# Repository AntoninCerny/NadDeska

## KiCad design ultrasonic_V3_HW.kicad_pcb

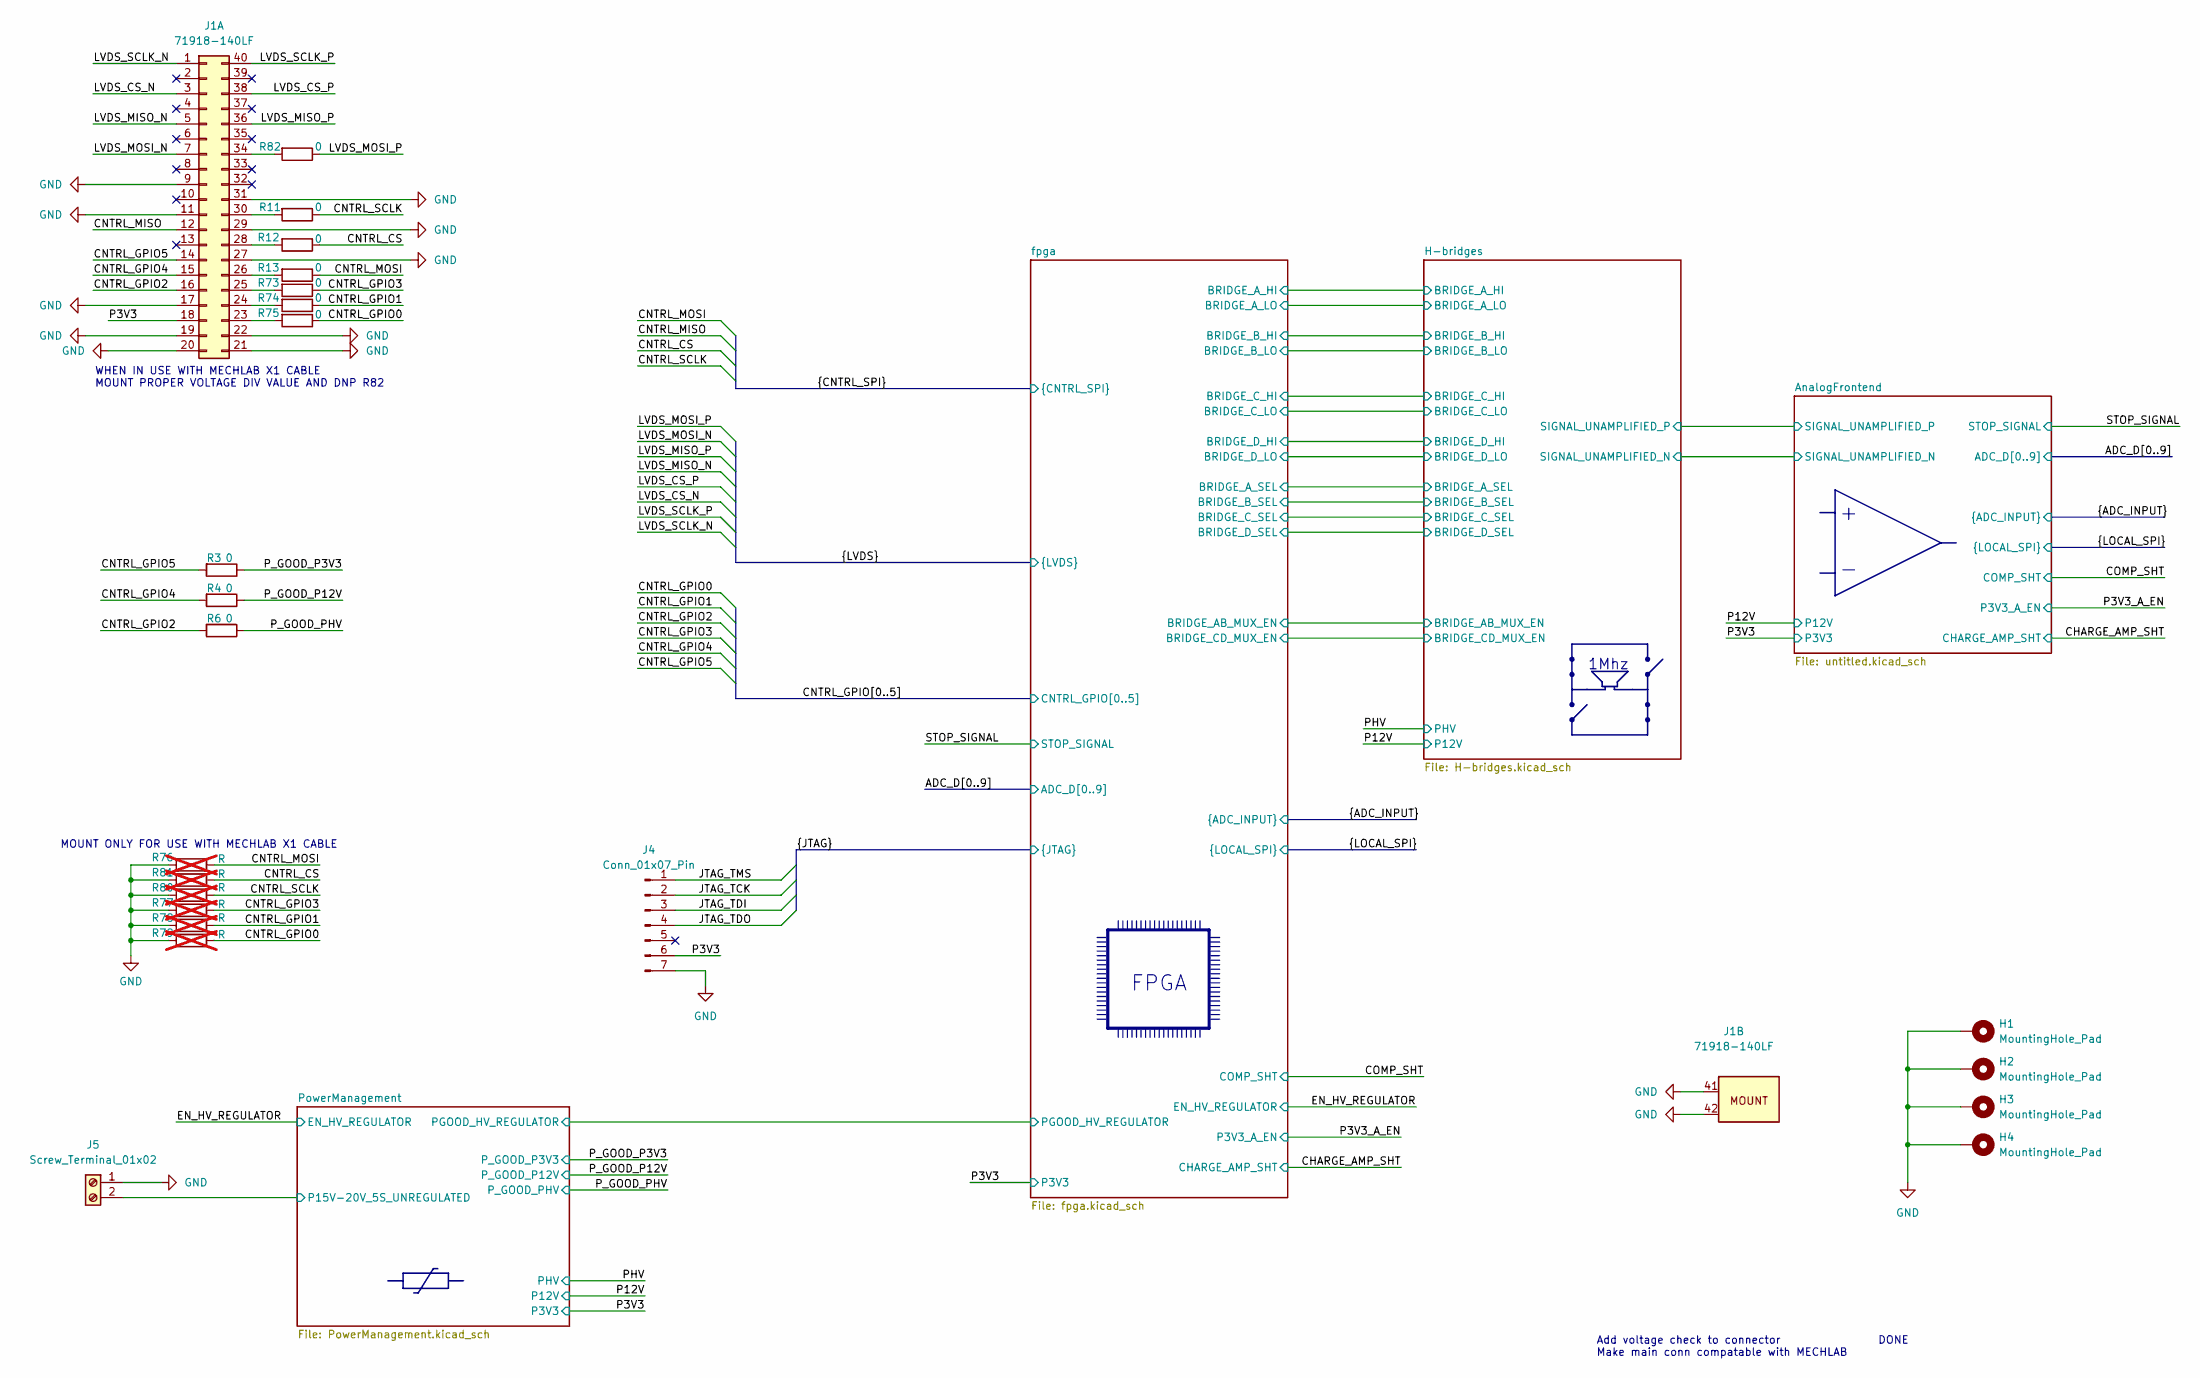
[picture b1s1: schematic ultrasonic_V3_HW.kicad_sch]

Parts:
H1, H2, H3, H4: MountingHole_Pad; MountingHole_3.2mm_M3_DIN965_Pad_TopBottom
J1: 71918-140LF; CON40_2X20_USZ_FCI_GLE
J4: Conn_01x07_Pin; PinHeader_1x07_P2.54mm_Vertical
J5: Screw_Terminal_01x02; TerminalBlock_Phoenix_MKDS-1,5-2-5.08_1x02_P5.08mm_Horizont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
R3, R4, R6, R11, R12, R13, R73, R74, R75, R82: 0; R_0603_1608Metric_Pad0.98x0.95mm_HandSolder
R76, R77, R78, R79, R80, R81: R; R_0603_1608Metric_Pad0.98x0.95mm_HandSolder; not fitted

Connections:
/CNTRL_CS: R12.1, R81.1; also elsewhere on the board
/CNTRL_GPIO0: R75.1, R79.1; also elsewhere on the board
/CNTRL_GPIO1: R74.1, R78.1; also elsewhere on the board
/CNTRL_GPIO2: J1.16, R6.2; also elsewhere on the board
/CNTRL_GPIO3: R73.1, R77.1; also elsewhere on the board
/CNTRL_GPIO4: J1.15, R4.2; also elsewhere on the board
/CNTRL_GPIO5: J1.14, R3.2; also elsewhere on the board
/CNTRL_MISO: J1.12; also elsewhere on the board
/CNTRL_MOSI: R13.1, R76.1; also elsewhere on the board
/CNTRL_SCLK: R11.1, R80.1; also elsewhere on the board
/JTAG_TCK: J4.2; also elsewhere on the board
/JTAG_TDI: J4.3; also elsewhere on the board
/JTAG_TDO: J4.4; also elsewhere on the board
/JTAG_TMS: J4.1; also elsewhere on the board
/LVDS_CS_N: J1.3; also elsewhere on the board
/LVDS_CS_P: J1.38; also elsewhere on the board
/LVDS_MISO_N: J1.5; also elsewhere on the board
/LVDS_MISO_P: J1.36; also elsewhere on the board
/LVDS_MOSI_N: J1.7; also elsewhere on the board
/LVDS_MOSI_P: R82.1; also elsewhere on the board
/LVDS_SCLK_N: J1.1; also elsewhere on the board
/LVDS_SCLK_P: J1.40; also elsewhere on the board
/P3V3: J1.18, J4.6; also elsewhere on the board
/P_GOOD_P3V3: R3.1; also elsewhere on the board
/P_GOOD_P12V: R4.1; also elsewhere on the board
/P_GOOD_PHV: R6.1; also elsewhere on the board
/PowerManagement/P15V-20V_5S_UNREGULATED: J5.2; also elsewhere on the board
GND: H1.1, H2.1, H3.1, H4.1, J1.9, J1.11, J1.17, J1.19, J1.20, J1.21, J1.22, J1.27, J1.29, J1.31, J1.41 (MOUNT_HOLE), J1.42 (MOUNT_HOLE), J4.7, J5.1, R76.2, R77.2, R78.2, R79.2, R80.2, R81.2; also elsewhere on the board
unnamed: J1.23, R75.2
unnamed: J1.24, R74.2
unnamed: J1.25, R73.2
unnamed: J1.26, R13.2
unnamed: J1.28, R12.2
unnamed: J1.30, R11.2
unnamed: J1.34, R82.2

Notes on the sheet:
FPGA
WHEN IN USE WITH MECHLAB X1 CABLE MOUNT PROPER VOLTAGE DIV VALUE AND DNP R82
Add voltage check to connector DONE Make main conn compatable with MECHLAB
MOUNT ONLY FOR USE WITH MECHLAB X1 CABLE
1Mhz

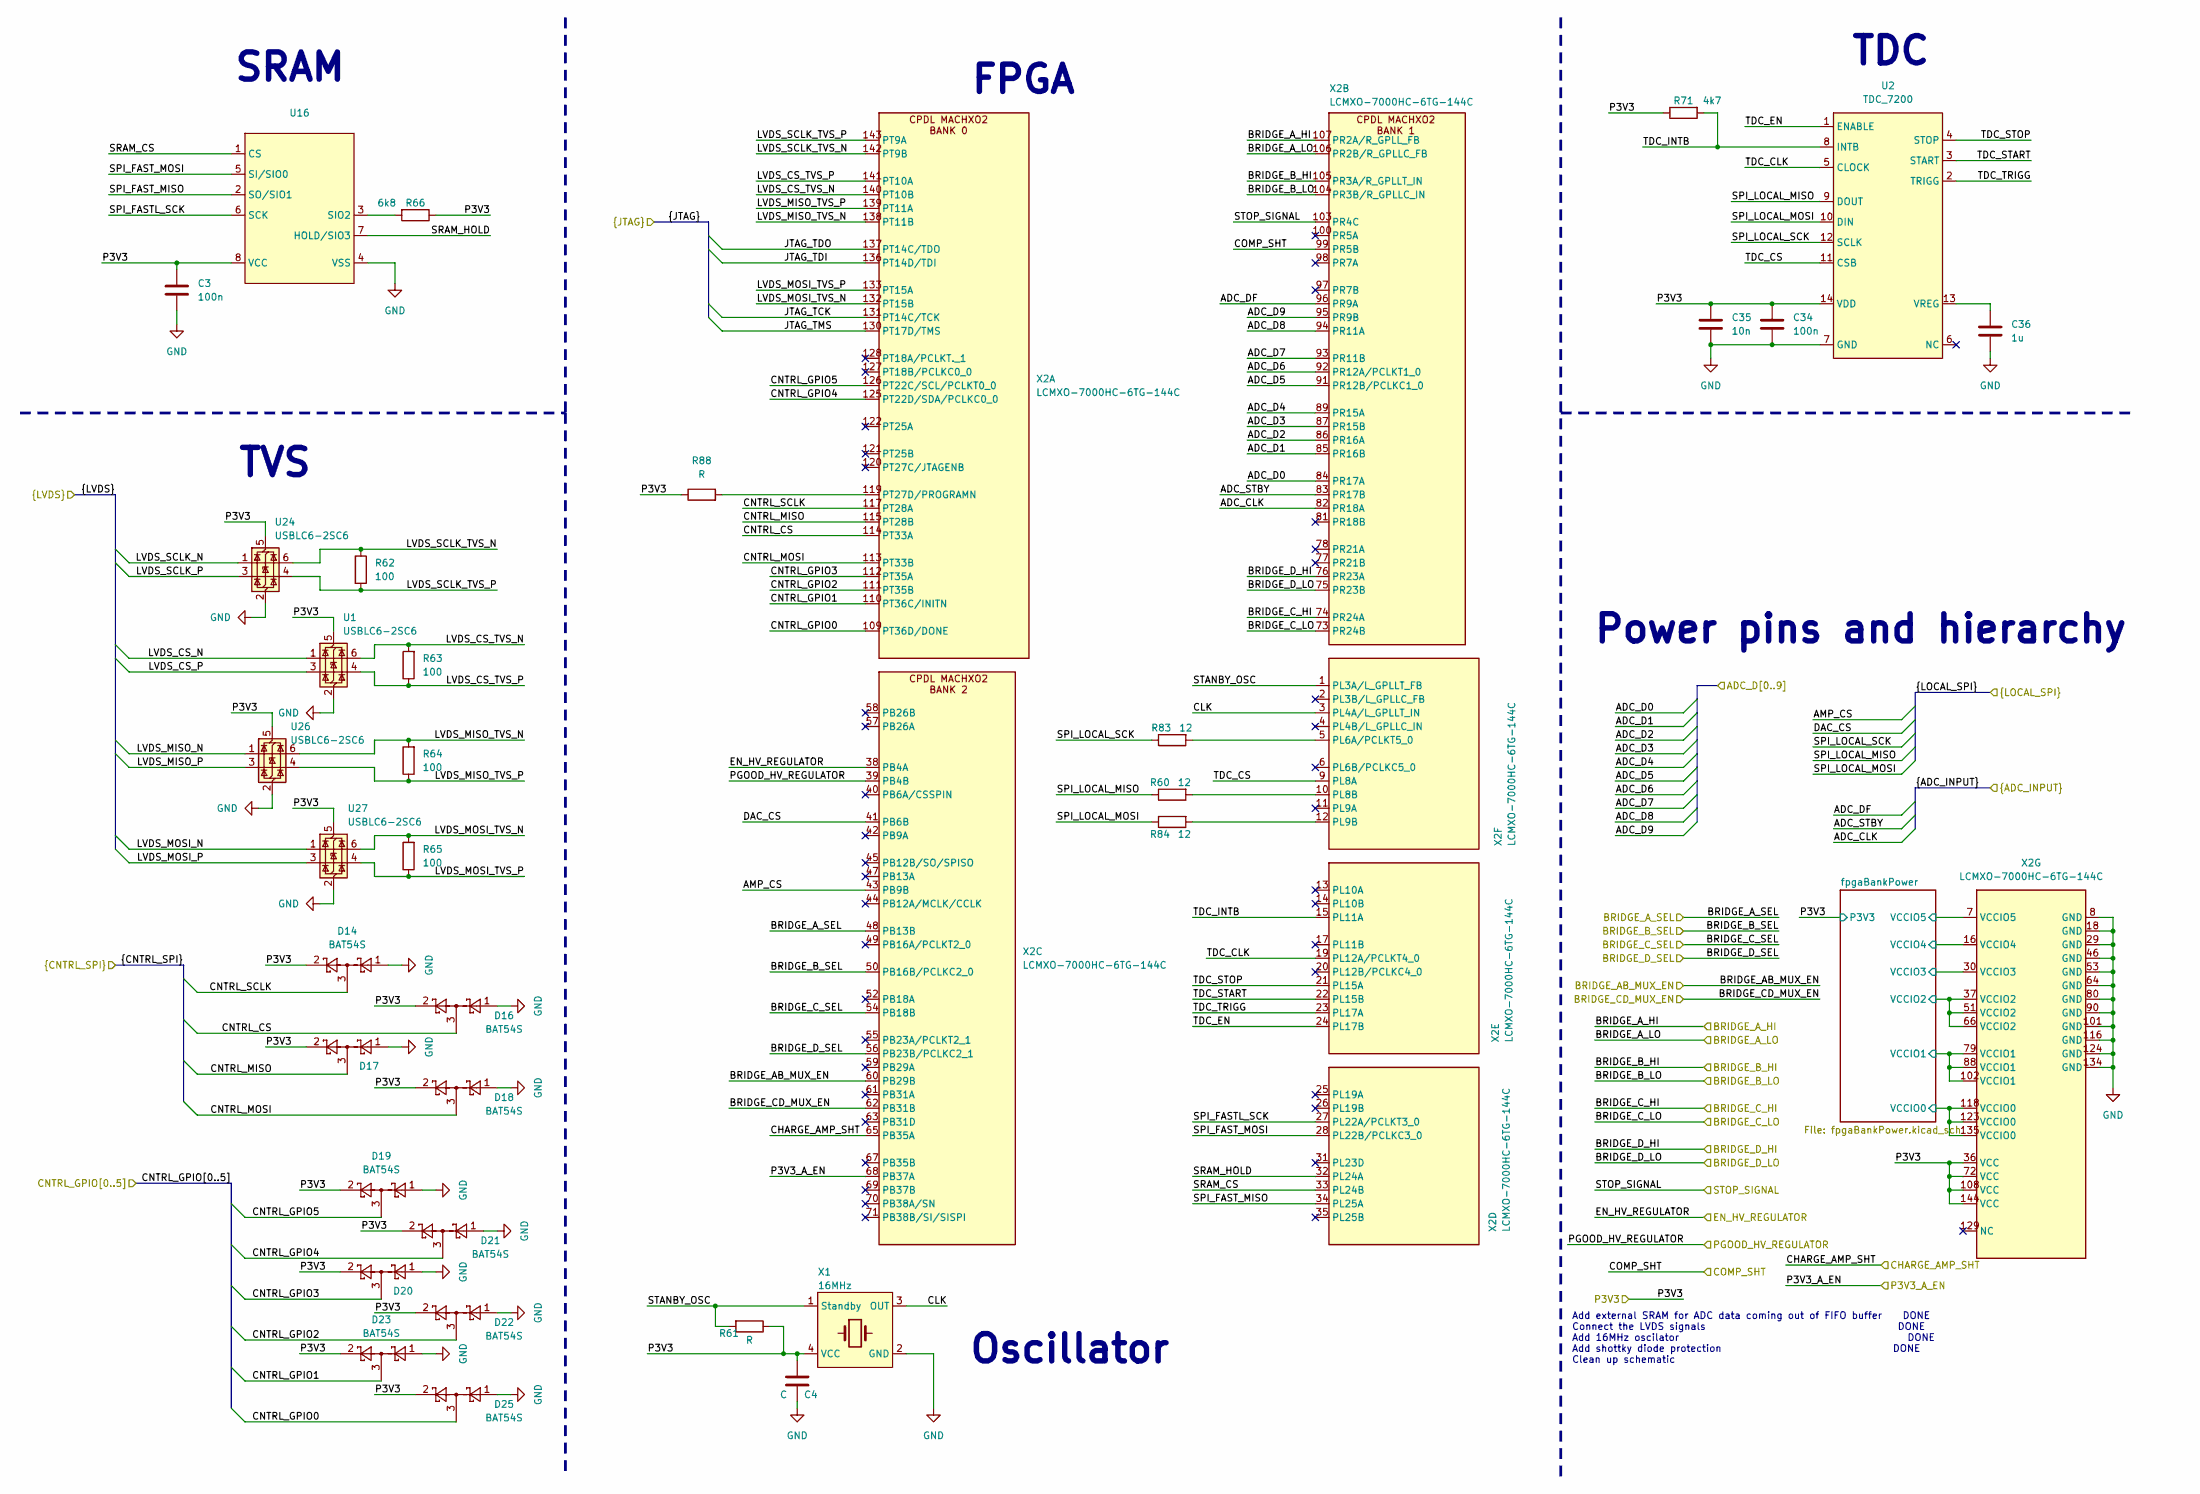
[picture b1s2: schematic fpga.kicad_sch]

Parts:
C3, C34: 100n; C_0603_1608Metric_Pad1.08x0.95mm_HandSolder
C4: C; C_0603_1608Metric
C35: 10n; C_0603_1608Metric_Pad1.08x0.95mm_HandSolder
C36: 1u; C_0603_1608Metric_Pad1.08x0.95mm_HandSolder
D14, D16, D17, D18, D19, D20, D21, D22, D23, D25: BAT54S; SOT-23
R60, R83, R84: 12; R_0603_1608Metric
R61: R; R_0603_1608Metric
R62, R63, R64, R65: 100; C_0603_1608Metric_Pad1.08x0.95mm_HandSolder
R66: 6k8; R_0603_1608Metric
R71: 4k7; R_0603_1608Metric
R88: R; C_0603_1608Metric_Pad1.08x0.95mm_HandSolder
U1, U24, U26, U27: USBLC6-2SC6; SOT-23-6
U2: TDC_7200; TSSOP-14_4.4x5mm_P0.65mm
U16: SOIC-8_3.9x4.9mm_P1.27mm
X1: 16MHz; Crystal_SMD_5032-4Pin_5.0x3.2mm
X2: LCMXO-7000HC-6TG-144C; TQFP-144_20x20mm_P0.5mm

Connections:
/ADC_CLK: X2.82 (PR18A); also elsewhere on the board
/ADC_D0: X2.84 (PR17A); also elsewhere on the board
/ADC_D1: X2.85 (PR16B); also elsewhere on the board
/ADC_D2: X2.86 (PR16A); also elsewhere on the board
/ADC_D3: X2.87 (PR15B); also elsewhere on the board
/ADC_D4: X2.89 (PR15A); also elsewhere on the board
/ADC_D5: X2.91 (PR12B/PCLKC1_0); also elsewhere on the board
/ADC_D6: X2.92 (PR12A/PCLKT1_0); also elsewhere on the board
/ADC_D7: X2.93 (PR11B); also elsewhere on the board
/ADC_D8: X2.94 (PR11A); also elsewhere on the board
/ADC_D9: X2.95 (PR9B); also elsewhere on the board
/ADC_DF: X2.96 (PR9A); also elsewhere on the board
/ADC_STBY: X2.83 (PR17B); also elsewhere on the board
/AMP_CS: X2.43 (PB9B); also elsewhere on the board
/CHARGE_AMP_SHT: X2.65 (PB35A); also elsewhere on the board
/CNTRL_CS: D16.3 (COM), X2.114 (PT33A); also elsewhere on the board
/CNTRL_GPIO0: D25.3 (COM), X2.109 (PT36D/DONE); also elsewhere on the board
/CNTRL_GPIO1: D23.3 (COM), X2.110 (PT36C/INITN); also elsewhere on the board
/CNTRL_GPIO2: D22.3 (COM), X2.111 (PT35B); also elsewhere on the board
/CNTRL_GPIO3: D20.3 (COM), X2.112 (PT35A); also elsewhere on the board
/CNTRL_GPIO4: D21.3 (COM), X2.125 (PT22D/SDA/PCLKC0_0); also elsewhere on the board
/CNTRL_GPIO5: D19.3 (COM), X2.126 (PT22C/SCL/PCLKT0_0); also elsewhere on the board
/CNTRL_MISO: D17.3 (COM), X2.115 (PT28B); also elsewhere on the board
/CNTRL_MOSI: D18.3 (COM), X2.113 (PT33B); also elsewhere on the board
/CNTRL_SCLK: D14.3 (COM), X2.117 (PT28A); also elsewhere on the board
/COMP_SHT: X2.99 (PR5B); also elsewhere on the board
/DAC_CS: X2.41 (PB6B); also elsewhere on the board
/EN_HV_REGULATOR: X2.38 (PB4A); also elsewhere on the board
/H-bridges/BRIDGE_AB_MUX_EN: X2.60 (PB29B); also elsewhere on the board
/H-bridges/BRIDGE_CD_MUX_EN: X2.62 (PB31B); also elsewhere on the board
/JTAG_TCK: X2.131 (PT14C/TCK); also elsewhere on the board
/JTAG_TDI: X2.136 (PT14D/TDI); also elsewhere on the board
/JTAG_TDO: X2.137 (PT14C/TDO); also elsewhere on the board
/JTAG_TMS: X2.130 (PT17D/TMS); also elsewhere on the board
/LVDS_CS_N: U1.1 (I/O1); also elsewhere on the board
/LVDS_CS_P: U1.3 (I/O2); also elsewhere on the board
/LVDS_MISO_N: U26.1 (I/O1); also elsewhere on the board
/LVDS_MISO_P: U26.3 (I/O2); also elsewhere on the board
/LVDS_MOSI_N: U27.1 (I/O1); also elsewhere on the board
/LVDS_MOSI_P: U27.3 (I/O2); also elsewhere on the board
/LVDS_SCLK_N: U24.1 (I/O1); also elsewhere on the board
/LVDS_SCLK_P: U24.3 (I/O2); also elsewhere on the board
/P3V3: C3.2, C4.2, C34.1, C35.1, D14.2 (K), D16.2 (K), D17.2 (K), D18.2 (K), D19.2 (K), D20.2 (K), D21.2 (K), D22.2 (K), D23.2 (K), D25.2 (K), R61.1, R66.1, R71.1, R88.1, U1.5 (VBUS), U2.14 (VDD), U16.8 (VCC), U24.5 (VBUS), U26.5 (VBUS), U27.5 (VBUS), X1.4 (VCC), X2.36 (VCC), X2.72 (VCC), X2.108 (VCC), X2.144 (VCC); also elsewhere on the board
/P3V3_A_EN: X2.68 (PB37A); also elsewhere on the board
/SPI_LOCAL_MISO: R60.1, U2.9 (DOUT)
/SPI_LOCAL_MOSI: R84.1, U2.10 (DIN); also elsewhere on the board
/SPI_LOCAL_SCK: R83.1, U2.12 (SCLK); also elsewhere on the board
/STOP_SIGNAL: X2.103 (PR4C); also elsewhere on the board
/fpga/BRIDGE_A_HI: X2.107 (PR2A/R_GPLL_FB); also elsewhere on the board
/fpga/BRIDGE_A_LO: X2.106 (PR2B/R_GPLLC_FB); also elsewhere on the board
/fpga/BRIDGE_A_SEL: X2.48 (PB13B); also elsewhere on the board
/fpga/BRIDGE_B_HI: X2.105 (PR3A/R_GPLLT_IN); also elsewhere on the board
/fpga/BRIDGE_B_LO: X2.104 (PR3B/R_GPLLC_IN); also elsewhere on the board
/fpga/BRIDGE_B_SEL: X2.50 (PB16B/PCLKC2_0); also elsewhere on the board
/fpga/BRIDGE_C_HI: X2.74 (PR24A); also elsewhere on the board
/fpga/BRIDGE_C_LO: X2.73 (PR24B); also elsewhere on the board
/fpga/BRIDGE_C_SEL: X2.54 (PB18B); also elsewhere on the board
/fpga/BRIDGE_D_HI: X2.76 (PR23A); also elsewhere on the board
/fpga/BRIDGE_D_LO: X2.75 (PR23B); also elsewhere on the board
/fpga/BRIDGE_D_SEL: X2.56 (PB23B/PCLKC2_1); also elsewhere on the board
/fpga/CLK: X1.3 (OUT), X2.3 (PL4A/L_GPLLT_IN)
/fpga/LVDS_CS_TVS_N: R63.2, U1.6 (I/O1), X2.140 (PT10B)
/fpga/LVDS_CS_TVS_P: R63.1, U1.4 (I/O2), X2.141 (PT10A)
/fpga/LVDS_MISO_TVS_N: R64.2, U26.6 (I/O1), X2.138 (PT11B)
/fpga/LVDS_MISO_TVS_P: R64.1, U26.4 (I/O2), X2.139 (PT11A)
/fpga/LVDS_MOSI_TVS_N: R65.2, U27.6 (I/O1), X2.132 (PT15B)
/fpga/LVDS_MOSI_TVS_P: R65.1, U27.4 (I/O2), X2.133 (PT15A)
/fpga/LVDS_SCLK_TVS_N: R62.1, U24.6 (I/O1), X2.142 (PT9B)
/fpga/LVDS_SCLK_TVS_P: R62.2, U24.4 (I/O2), X2.143 (PT9A)
/fpga/PGOOD_HV_REGULATOR: X2.39 (PB4B); also elsewhere on the board
/fpga/SPI_FASTL_SCK: U16.6 (SCK), X2.27 (PL22A/PCLKT3_0)
/fpga/SPI_FAST_MISO: U16.2 (SO/SIO1), X2.34 (PL25A)
/fpga/SPI_FAST_MOSI: U16.5 (SI/SIO0), X2.28 (PL22B/PCLKC3_0)
/fpga/SRAM_CS: U16.1 (CS), X2.33 (PL24B)
/fpga/SRAM_HOLD: U16.7 (HOLD/SIO3), X2.32 (PL24A)
/fpga/STANBY_OSC: R61.2, X1.1 (Standby), X2.1 (PL3A/L_GPLLT_FB)
/fpga/TDC_CLK: U2.5 (CLOCK), X2.19 (PL12A/PCLKT4_0)
/fpga/TDC_CS: U2.11 (CSB), X2.9 (PL8A)
/fpga/TDC_EN: U2.1 (ENABLE), X2.24 (PL17B)
/fpga/TDC_INTB: R71.2, U2.8 (INTB), X2.15 (PL11A)
/fpga/TDC_START: U2.3 (START), X2.22 (PL15B)
/fpga/TDC_STOP: U2.4 (STOP), X2.21 (PL15A)
/fpga/TDC_TRIGG: U2.2 (TRIGG), X2.23 (PL17A)
/fpga/fpgaBankPower/VCCIO0: X2.118 (VCCIO0), X2.123 (VCCIO0), X2.135 (VCCIO0); also elsewhere on the board
/fpga/fpgaBankPower/VCCIO1: X2.79 (VCCIO1), X2.88 (VCCIO1), X2.102 (VCCIO1); also elsewhere on the board
/fpga/fpgaBankPower/VCCIO2: X2.37 (VCCIO2), X2.51 (VCCIO2), X2.66 (VCCIO2); also elsewhere on the board
/fpga/fpgaBankPower/VCCIO3: X2.30 (VCCIO3); also elsewhere on the board
/fpga/fpgaBankPower/VCCIO4: X2.16 (VCCIO4); also elsewhere on the board
/fpga/fpgaBankPower/VCCIO5: X2.7 (VCCIO5); also elsewhere on the board
GND: C3.1, C4.1, C34.2, C35.2, C36.2, D14.1 (A), D16.1 (A), D17.1 (A), D18.1 (A), D19.1 (A), D20.1 (A), D21.1 (A), D22.1 (A), D23.1 (A), D25.1 (A), U1.2 (GND), U2.7 (GND), U16.4 (VSS), U24.2 (GND), U26.2 (GND), U27.2 (GND), X1.2 (GND), X2.8 (GND), X2.18 (GND), X2.29 (GND), X2.46 (GND), X2.53 (GND), X2.64 (GND), X2.80 (GND), X2.90 (GND), X2.101 (GND), X2.116 (GND), X2.124 (GND), X2.134 (GND); also elsewhere on the board
unnamed: C36.1, U2.13 (VREG)
unnamed: R66.2, U16.3 (SIO2)
unnamed: R88.2, X2.119 (PT27D/PROGRAMN)
unnamed: R83.2, X2.5 (PL6A/PCLKT5_0)
unnamed: R60.2, X2.10 (PL8B)
unnamed: R84.2, X2.12 (PL9B)

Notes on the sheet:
TVS
SRAM
TDC
Power pins and hierarchy
Add external SRAM for ADC data coming out of FIFO buffer DONE Connect the LVDS signals DONE Add 16MHz oscilator DONE Add shottky diode protection DONE Clean up schematic
Oscillator
FPGA

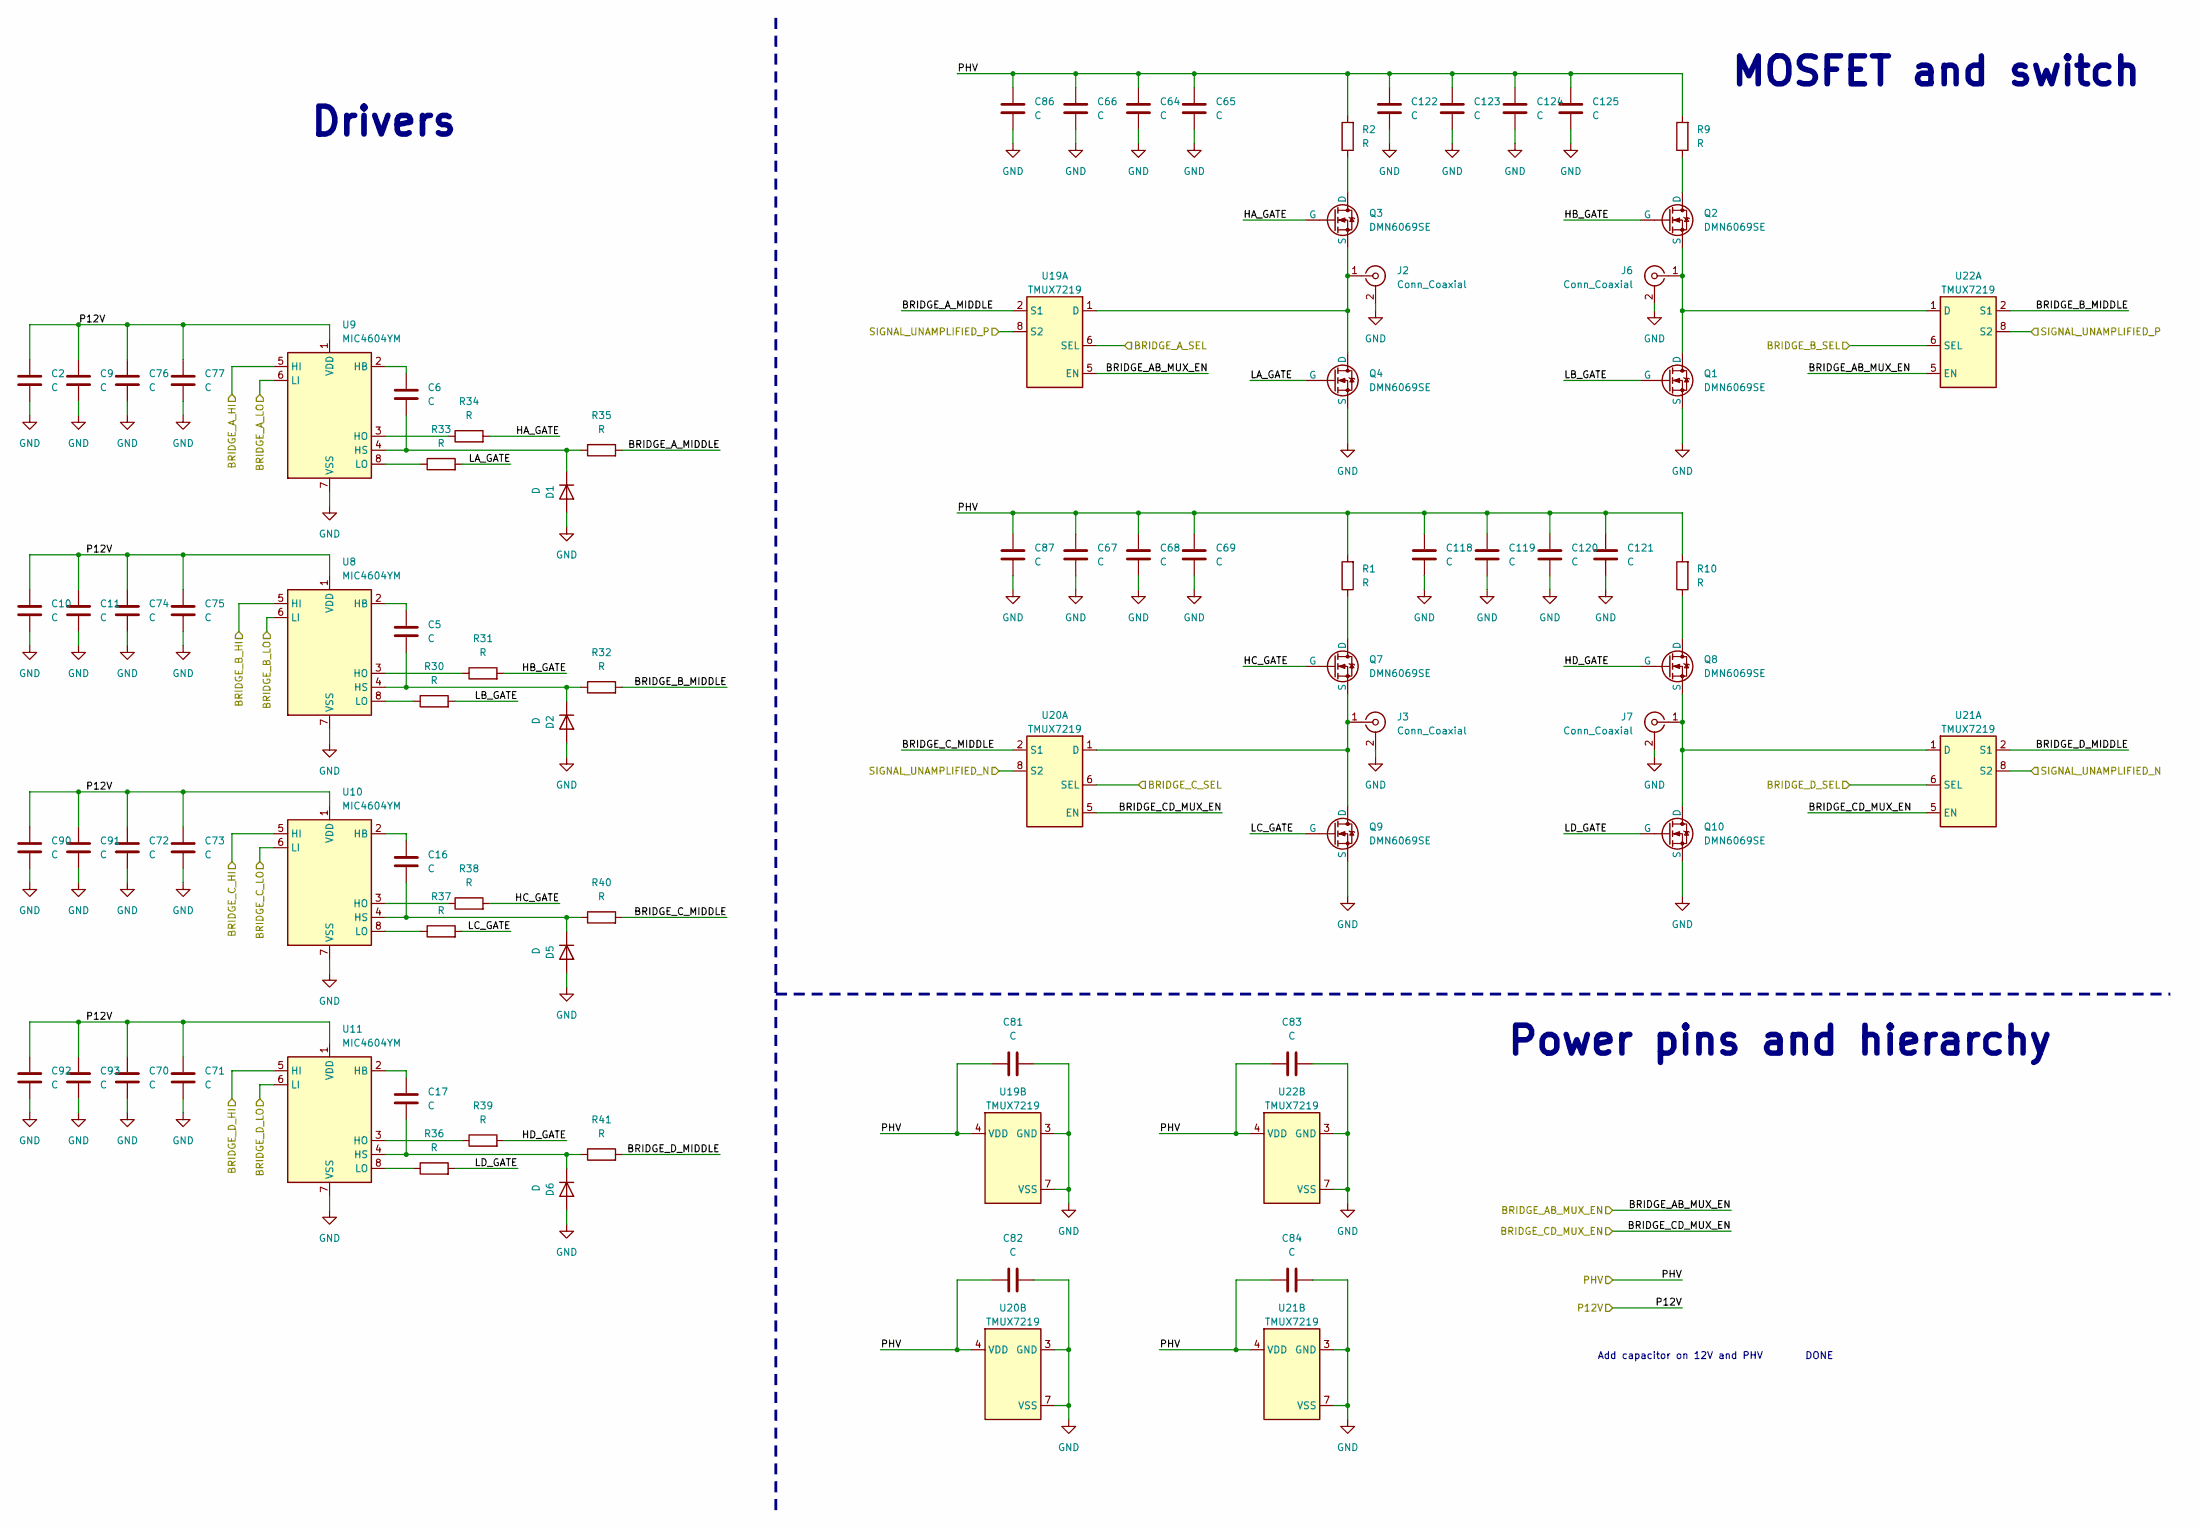
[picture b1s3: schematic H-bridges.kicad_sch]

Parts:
C2, C5, C6, C10, C16, C17, C66, C67, C70, C72, C74, C76, C81, C82, C83, C84, C86, C87, C90, C92, C118, C119, C122, C123: C; C_0603_1608Metric_Pad1.08x0.95mm_HandSolder
C9, C11, C64, C65, C68, C69, C71, C73, C75, C77, C91, C93, C120, C121, C124, C125: C; C_0805_2012Metric_Pad1.18x1.45mm_HandSolder
D1, D2, D5, D6: D; D_SOD-123
J2, J3, J6, J7: Conn_Coaxial; SMA_Amphenol_901-144_Vertical
Q1, Q2, Q3, Q4, Q7, Q8, Q9, Q10: DMN6069SE; SOT-223-3_TabPin2
R1, R2, R9, R10: R; R_1206_3216Metric_Pad1.30x1.75mm_HandSolder
R30, R31, R32, R33, R34, R35, R36, R37, R38, R39, R40, R41: R; R_0603_1608Metric_Pad0.98x0.95mm_HandSolder
U8, U9, U10, U11: MIC4604YM; SOIC-8_3.9x4.9mm_P1.27mm
U19, U20, U21, U22: TMUX7219; VSSOP-8_3.0x3.0mm_P0.65mm

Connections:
/AnalogFrontend/SIGNAL_UNAMPLIFIED_N: U20.8 (S2), U21.8 (S2); also elsewhere on the board
/AnalogFrontend/SIGNAL_UNAMPLIFIED_P: U19.8 (S2), U22.8 (S2); also elsewhere on the board
/H-bridges/BRIDGE_AB_MUX_EN: U19.5 (EN), U22.5 (EN); also elsewhere on the board
/H-bridges/BRIDGE_A_MIDDLE: R35.2, U19.2 (S1)
/H-bridges/BRIDGE_B_MIDDLE: R32.2, U22.2 (S1)
/H-bridges/BRIDGE_CD_MUX_EN: U20.5 (EN), U21.5 (EN); also elsewhere on the board
/H-bridges/BRIDGE_C_MIDDLE: R40.2, U20.2 (S1)
/H-bridges/BRIDGE_D_MIDDLE: R41.2, U21.2 (S1)
/H-bridges/HA_GATE: Q3.1 (G), R34.2
/H-bridges/HB_GATE: Q2.1 (G), R31.2
/H-bridges/HC_GATE: Q7.1 (G), R38.2
/H-bridges/HD_GATE: Q8.1 (G), R39.2
/H-bridges/LA_GATE: Q4.1 (G), R33.2
/H-bridges/LB_GATE: Q1.1 (G), R30.2
/H-bridges/LC_GATE: Q9.1 (G), R37.2
/H-bridges/LD_GATE: Q10.1 (G), R36.2
/P12V: C2.1, C9.2, C10.1, C11.2, C70.1, C71.2, C72.1, C73.2, C74.1, C75.2, C76.1, C77.2, C90.1, C91.2, C92.1, C93.2, U8.1 (VDD), U9.1 (VDD), U10.1 (VDD), U11.1 (VDD); also elsewhere on the board
/PHV: C64.2, C65.2, C66.1, C67.1, C68.2, C69.2, C81.1, C82.1, C83.1, C84.1, C86.1, C87.1, C118.1, C119.1, C120.2, C121.2, C122.1, C123.1, C124.2, C125.2, R1.2, R2.2, R9.2, R10.2, U19.4 (VDD), U20.4 (VDD), U21.4 (VDD), U22.4 (VDD); also elsewhere on the board
/fpga/BRIDGE_A_HI: U9.5 (HI); also elsewhere on the board
/fpga/BRIDGE_A_LO: U9.6 (LI); also elsewhere on the board
/fpga/BRIDGE_A_SEL: U19.6 (SEL); also elsewhere on the board
/fpga/BRIDGE_B_HI: U8.5 (HI); also elsewhere on the board
/fpga/BRIDGE_B_LO: U8.6 (LI); also elsewhere on the board
/fpga/BRIDGE_B_SEL: U22.6 (SEL); also elsewhere on the board
/fpga/BRIDGE_C_HI: U10.5 (HI); also elsewhere on the board
/fpga/BRIDGE_C_LO: U10.6 (LI); also elsewhere on the board
/fpga/BRIDGE_C_SEL: U20.6 (SEL); also elsewhere on the board
/fpga/BRIDGE_D_HI: U11.5 (HI); also elsewhere on the board
/fpga/BRIDGE_D_LO: U11.6 (LI); also elsewhere on the board
/fpga/BRIDGE_D_SEL: U21.6 (SEL); also elsewhere on the board
GND: C2.2, C9.1, C10.2, C11.1, C64.1, C65.1, C66.2, C67.2, C68.1, C69.1, C70.2, C71.1, C72.2, C73.1, C74.2, C75.1, C76.2, C77.1, C81.2, C82.2, C83.2, C84.2, C86.2, C87.2, C90.2, C91.1, C92.2, C93.1, C118.2, C119.2, C120.1, C121.1, C122.2, C123.2, C124.1, C125.1, D1.2 (A), D2.2 (A), D5.2 (A), D6.2 (A), J2.2 (Ext), J3.2 (Ext), J6.2 (Ext), J7.2 (Ext), Q1.3 (S), Q4.3 (S), Q9.3 (S), Q10.3 (S), U8.7 (VSS), U9.7 (VSS), U10.7 (VSS), U11.7 (VSS), U19.3 (GND), U19.7 (VSS), U20.3 (GND), U20.7 (VSS), U21.3 (GND), U21.7 (VSS), U22.3 (GND), U22.7 (VSS); also elsewhere on the board
unnamed: C6.2, D1.1 (K), R35.1, U9.4 (HS)
unnamed: C5.2, D2.1 (K), R32.1, U8.4 (HS)
unnamed: C16.2, D5.1 (K), R40.1, U10.4 (HS)
unnamed: C17.2, D6.1 (K), R41.1, U11.4 (HS)
unnamed: J2.1 (In), Q3.3 (S), Q4.2 (D), U19.1 (D)
unnamed: J3.1 (In), Q7.3 (S), Q9.2 (D), U20.1 (D)
unnamed: J6.1 (In), Q1.2 (D), Q2.3 (S), U22.1 (D)
unnamed: J7.1 (In), Q8.3 (S), Q10.2 (D), U21.1 (D)
unnamed: Q2.2 (D), R9.1
unnamed: Q3.2 (D), R2.1
unnamed: Q7.2 (D), R1.1
unnamed: Q8.2 (D), R10.1
unnamed: C5.1, U8.2 (HB)
unnamed: R31.1, U8.3 (HO)
unnamed: R30.1, U8.8 (LO)
unnamed: C6.1, U9.2 (HB)
unnamed: R34.1, U9.3 (HO)
unnamed: R33.1, U9.8 (LO)
unnamed: C16.1, U10.2 (HB)
unnamed: R38.1, U10.3 (HO)
unnamed: R37.1, U10.8 (LO)
unnamed: C17.1, U11.2 (HB)
unnamed: R39.1, U11.3 (HO)
unnamed: R36.1, U11.8 (LO)

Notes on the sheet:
Add capacitor on 12V and PHV DONE
Power pins and hierarchy
MOSFET and switch
Drivers
